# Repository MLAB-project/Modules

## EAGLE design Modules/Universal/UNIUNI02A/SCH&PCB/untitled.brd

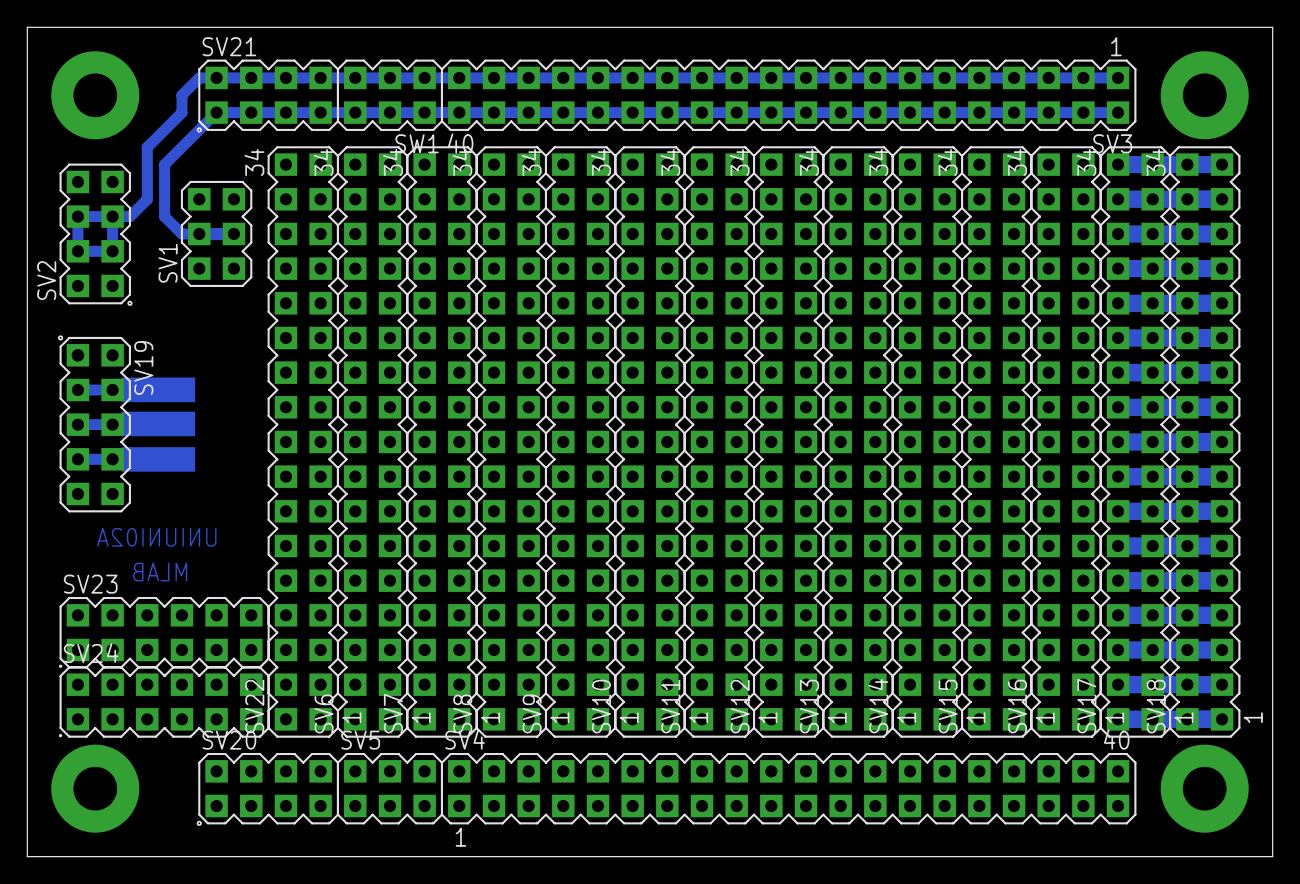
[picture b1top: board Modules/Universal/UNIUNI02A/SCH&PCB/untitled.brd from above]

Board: 2 copper layers, 91.2 x 60.8 mm, 29 parts (0 on the bottom side), 30 nets.

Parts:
SV1, SV5: MA03-2
SV2, SV20, SV21: MA04-2
SV3, SV4: MA20-2
SV6, SV7, SV8, SV9, SV10, SV11, SV12, SV13, SV14, SV15, SV16, SV17, SV18, SV22: MA17-2
SV19: MA05-2
SV23, SV24: MA06-2
SW1: MA03-2
X3, X4, X5, X6: SROUB3M

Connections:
+5V: SV1.3, SV1.4, SV3.2, SV3.4, SV3.6, SV3.8, SV3.10, SV3.12, SV3.14, SV3.16, SV3.18, SV3.20, SV3.22, SV3.24, SV3.26, SV3.28, SV3.30, SV3.32, SV3.34, SV3.36, SV3.38, SV3.40, SV21.1, SV21.3, SV21.5, SV21.7, SW1.2, SW1.4, SW1.6
+12V: SV2.3, SV2.4, SV2.5, SV2.6, SV3.1, SV3.3, SV3.5, SV3.7, SV3.9, SV3.11, SV3.13, SV3.15, SV3.17, SV3.19, SV3.21, SV3.23, SV3.25, SV3.27, SV3.29, SV3.31, SV3.33, SV3.35, SV3.37, SV3.39, SV21.2, SV21.4, SV21.6, SV21.8, SW1.1, SW1.3, SW1.5
GND: SV1.1, SV1.2, SV1.5, SV1.6, SV2.1, SV2.2, SV2.7, SV2.8, SV4.1, SV4.2, SV4.3, SV4.4, SV4.5, SV4.6, SV4.7, SV4.8, SV4.9, SV4.10, SV4.11, SV4.12, SV4.13, SV4.14, SV4.15, SV4.16, SV4.17, SV4.18, SV4.19, SV4.20, SV4.21, SV4.22, SV4.23, SV4.24, SV4.25, SV4.26, SV4.27, SV4.28, SV4.29, SV4.30, SV4.31, SV4.32, SV4.33, SV4.34, SV4.35, SV4.36, SV4.37, SV4.38, SV4.39, SV4.40, SV5.1, SV5.2, SV5.3, SV5.4, SV5.5, SV5.6, SV19.1, SV19.2, SV19.9, SV19.10, SV20.1, SV20.2, SV20.3, SV20.4, SV20.5, SV20.6, SV20.7, SV20.8, X3.P$1, X4.P$1, X5.P$1, X6.P$1
unnamed: SV19.3, SV19.4
unnamed: SV19.5, SV19.6
unnamed: SV19.7, SV19.8
unnamed: SV17.33, SV17.34, SV18.33, SV18.34
unnamed: SV17.31, SV17.32
unnamed: SV17.29, SV17.30, SV18.29, SV18.30
unnamed: SV17.27, SV17.28, SV18.27, SV18.28
unnamed: SV17.25, SV17.26, SV18.25, SV18.26
unnamed: SV17.23, SV17.24
unnamed: SV17.21, SV17.22, SV18.21, SV18.22
unnamed: SV17.19, SV17.20
unnamed: SV17.17, SV17.18
unnamed: SV17.15, SV17.16
unnamed: SV17.13, SV17.14, SV18.13, SV18.14
unnamed: SV17.11, SV17.12, SV18.11, SV18.12
unnamed: SV17.9, SV17.10
unnamed: SV17.7, SV17.8, SV18.7, SV18.8
unnamed: SV17.5, SV17.6, SV18.5, SV18.6
unnamed: SV17.3, SV17.4, SV18.3, SV18.4
unnamed: SV17.1, SV17.2
unnamed: SV18.31, SV18.32
unnamed: SV18.23, SV18.24
unnamed: SV18.19, SV18.20
unnamed: SV18.17, SV18.18
unnamed: SV18.15, SV18.16
unnamed: SV18.9, SV18.10
unnamed: SV18.1, SV18.2

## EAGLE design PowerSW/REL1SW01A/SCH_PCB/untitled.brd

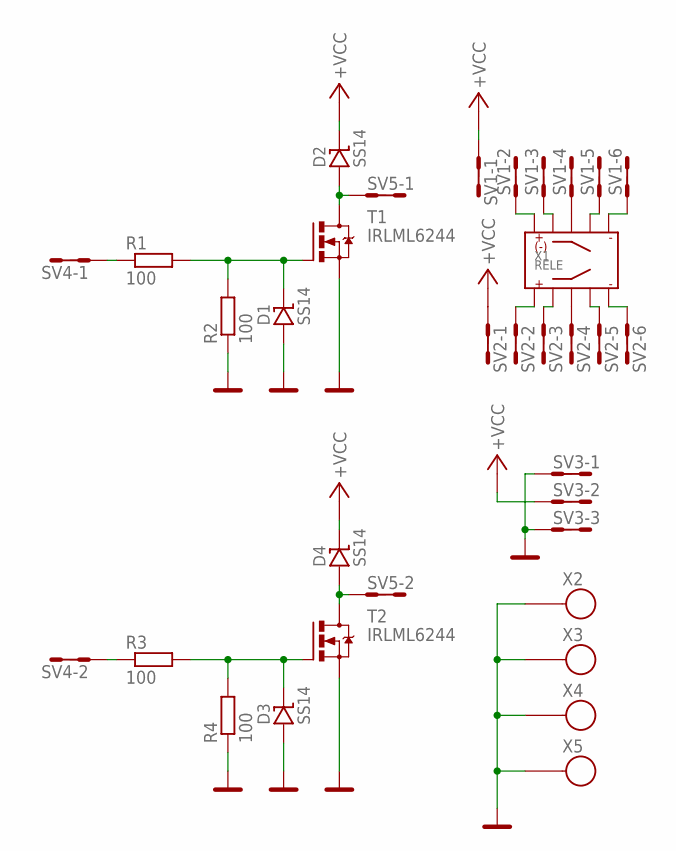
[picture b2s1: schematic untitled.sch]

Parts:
D1, D2, D3, D4: SS14; SMA
R1, R2, R3, R4: 100; 0805
SV1, SV2: MA06-2
SV3: MA03-2
SV4, SV5: MA02-2
T1, T2: IRLML6244; SOT23
X1: RELE
X2, X3, X4, X5: SROUB3M

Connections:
+VCC: D2.K, D4.K, SV1.1, SV1.2, SV2.1, SV2.2, SV3.3, SV3.4
GND: D1.A, D3.A, R2.1, R4.1, SV3.1, SV3.2, SV3.5, SV3.6, T1.2 (S), T2.2 (S), X2.P$1, X3.P$1, X4.P$1, X5.P$1
unnamed: D2.A, SV5.1, SV5.2, T1.3 (D)
unnamed: D1.K, R1.2, R2.2, T1.1 (G)
unnamed: D4.A, SV5.3, SV5.4, T2.3 (D)
unnamed: D3.K, R3.2, R4.2, T2.1 (G)
unnamed: SV1.3, SV1.4, X1.10
unnamed: SV1.5, SV1.6, X1.9
unnamed: SV1.7, SV1.8, X1.8
unnamed: SV1.9, SV1.10, X1.7
unnamed: SV1.11, SV1.12, X1.6
unnamed: SV2.3, SV2.4, X1.1
unnamed: SV2.5, SV2.6, X1.2
unnamed: SV2.7, SV2.8, X1.3
unnamed: SV2.9, SV2.10, X1.4
unnamed: SV2.11, SV2.12, X1.5
unnamed: R1.1, SV4.1, SV4.2
unnamed: R3.1, SV4.3, SV4.4

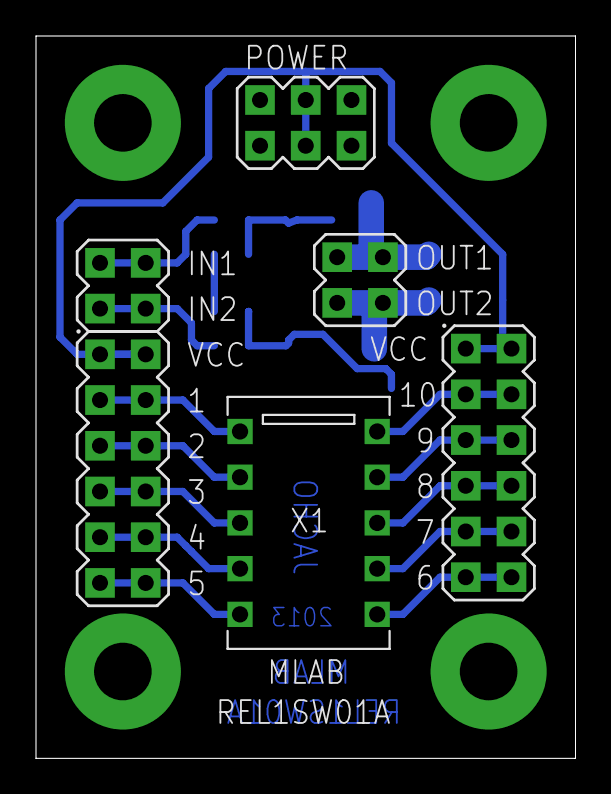
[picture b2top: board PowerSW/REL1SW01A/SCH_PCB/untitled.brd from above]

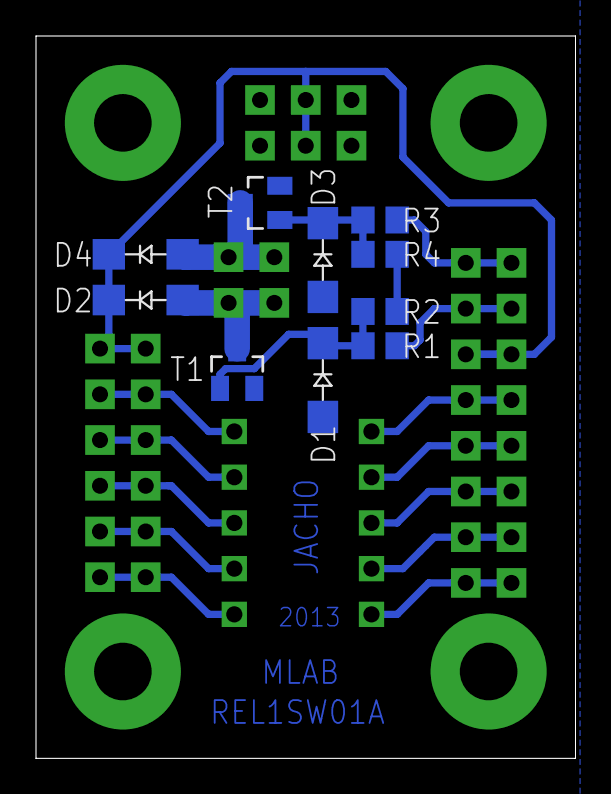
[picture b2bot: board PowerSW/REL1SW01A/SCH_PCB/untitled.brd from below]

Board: 2 copper layers, 30.0 x 40.1 mm, 20 parts (10 on the bottom side), 18 nets.

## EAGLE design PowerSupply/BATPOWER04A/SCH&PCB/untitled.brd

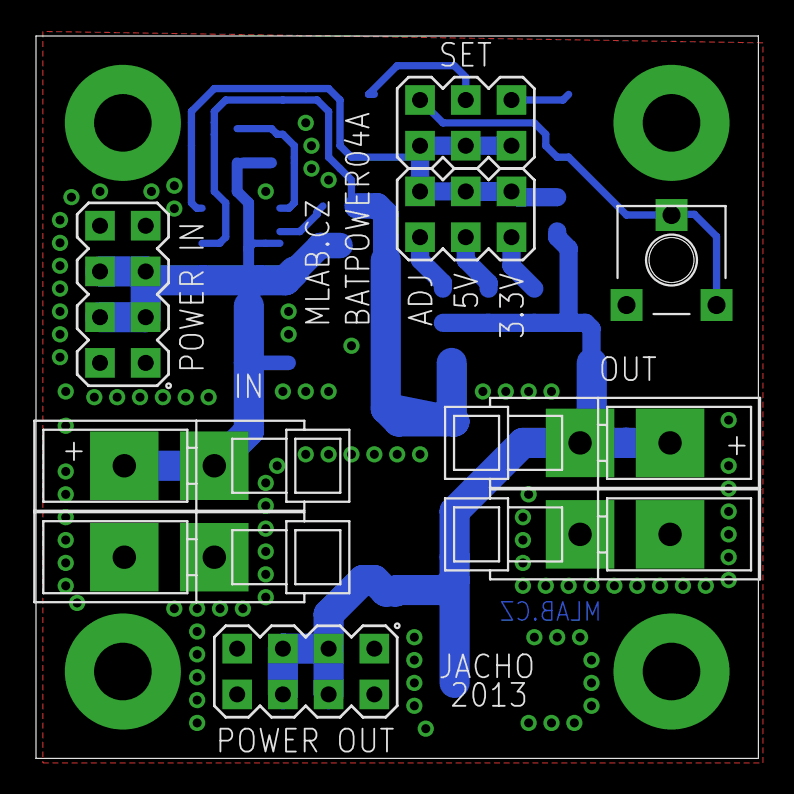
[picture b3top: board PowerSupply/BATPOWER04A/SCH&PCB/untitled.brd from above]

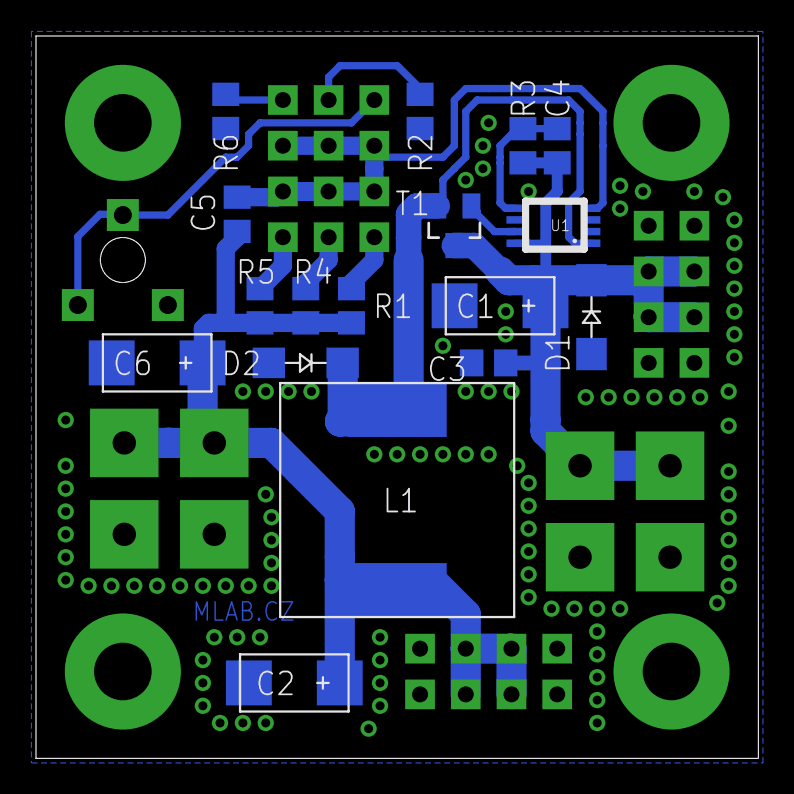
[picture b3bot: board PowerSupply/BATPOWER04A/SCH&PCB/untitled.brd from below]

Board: 2 copper layers, 40.1 x 40.1 mm, 30 parts (17 on the bottom side), 13 nets.

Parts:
C1: 47u; C
C2, C6: 100u; C
C3: 100n; C0805
C4: 1n; C0805
C5: 100p; C0805
D1: M4; SMA
D2: 15MQ040N; SMA
L1: 22u; DE1205-10
P1: TRIM_CA6XV
R1: 0805
R2, R6: 20k; 0805
R3: 22k; 0805
R4: 60k4; 0805
R5: 33k; 0805
SV1, SV2: MA04-2
SV3, SV4, SV5, SV6: WAGO256
SW1, SW2: MA03-2
T1: AP2305AGN; SOT23
U1: LM3485; MSOP-8
X1, X2, X3, X4: SROUB3M

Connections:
GND: C1.-, C2.-, C3.1, C6.-, D1.A, D2.A, P1.1, R2.1, R6.1, SV1.1, SV1.2, SV1.7, SV1.8, SV2.1, SV2.2, SV2.7, SV2.8, SV3.1, SV3.A1, SV5.1, SV5.A1, U1.2, U1.6
unnamed: T1.1, U1.7
unnamed: C1.+, C3.2, C4.2, D1.K, R3.2, SV1.3, SV1.4, SV1.5, SV1.6, SV4.1, SV4.A1, T1.3, U1.8
unnamed: C5.1, SW1.2, SW1.4, SW1.6, SW2.1, SW2.3, SW2.5, U1.4
unnamed: C4.1, R3.1, U1.5
unnamed: R1.1, SW1.1
unnamed: D2.K, L1.P$1, T1.2, U1.1
unnamed: R4.1, SW1.3
unnamed: C2.+, C5.2, C6.+, L1.P$2, R1.2, R4.2, R5.2, SV2.3, SV2.4, SV2.5, SV2.6, SV6.1, SV6.A1
unnamed: R5.1, SW1.5
unnamed: R2.2, SW2.4
unnamed: R6.2, SW2.6
unnamed: P1.2, P1.3, SW2.2

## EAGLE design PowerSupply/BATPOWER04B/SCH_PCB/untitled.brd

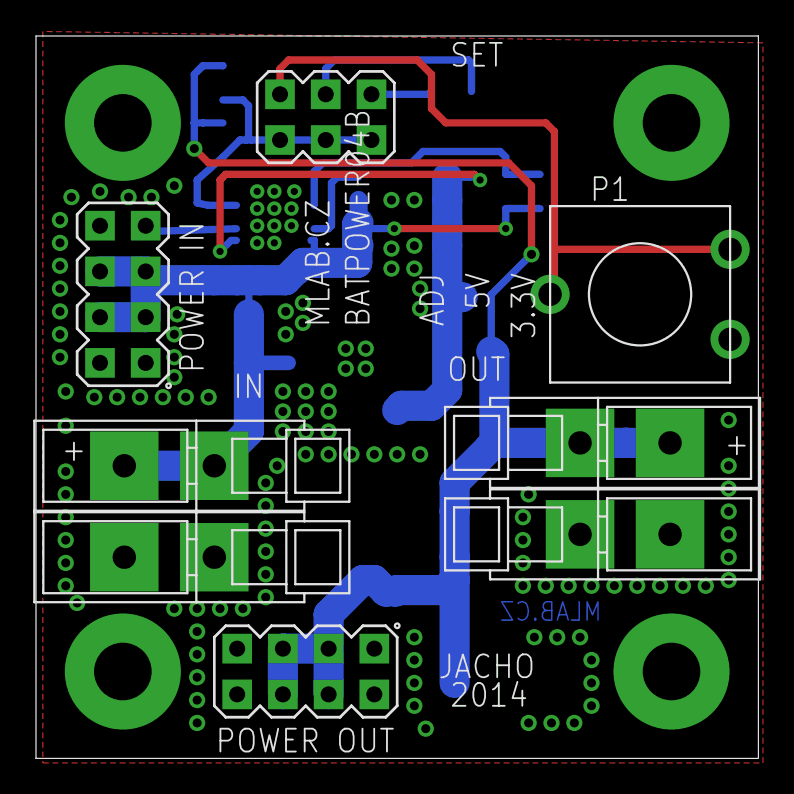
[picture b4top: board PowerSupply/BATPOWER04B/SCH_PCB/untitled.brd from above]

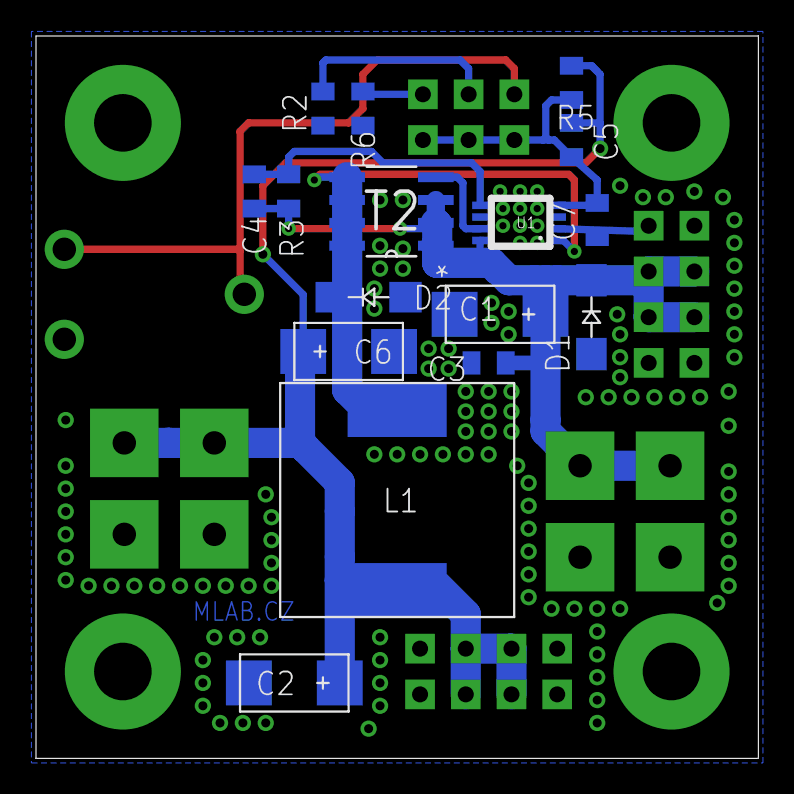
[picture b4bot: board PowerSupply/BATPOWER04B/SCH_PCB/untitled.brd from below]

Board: 2 copper layers, 40.1 x 40.1 mm, 28 parts (16 on the bottom side), 10 nets.

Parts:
C1: 47u; C
C2, C6: 100u; C
C3: 100n; C0805
C4: 1n; C0805
C5: 100p; C0805
C7: 470p; C0805
D1: M4; SMA
D2: 15MQ040N; SMA
L1: 22u; DE1205-10
P1: TRIM_CA9MTV10
R2, R6: 20k; 0805
R3: 22k; 0805
R5: 33k; 0805
SV1, SV2: MA04-2
SV3, SV4, SV5, SV6: WAGO256
SW2: MA03-2
T2: IRF7416; SO8
U1: LM3485; MSOP-8
X1, X2, X3, X4: SROUB3M

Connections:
GND: C1.-, C2.-, C3.1, C6.-, C7.1, D1.A, D2.A, P1.1, R2.1, R6.1, SV1.1, SV1.2, SV1.7, SV1.8, SV2.1, SV2.2, SV2.7, SV2.8, SV3.1, SV3.A1, SV5.1, SV5.A1, U1.2, U1.6
unnamed: T2.4, U1.7
unnamed: C1.+, C3.2, C4.2, D1.K, R3.2, SV1.3, SV1.4, SV1.5, SV1.6, SV4.1, SV4.A1, T2.1, T2.2, T2.3, U1.8
unnamed: C5.1, C7.2, R5.1, SW2.1, SW2.3, SW2.5, U1.4
unnamed: C4.1, R3.1, U1.5
unnamed: C2.+, C5.2, C6.+, L1.P$2, R5.2, SV2.3, SV2.4, SV2.5, SV2.6, SV6.1, SV6.A1
unnamed: D2.K, L1.P$1, T2.5, T2.6, T2.7, T2.8, U1.1
unnamed: R2.2, SW2.4
unnamed: R6.2, SW2.6
unnamed: P1.2, P1.3, SW2.2

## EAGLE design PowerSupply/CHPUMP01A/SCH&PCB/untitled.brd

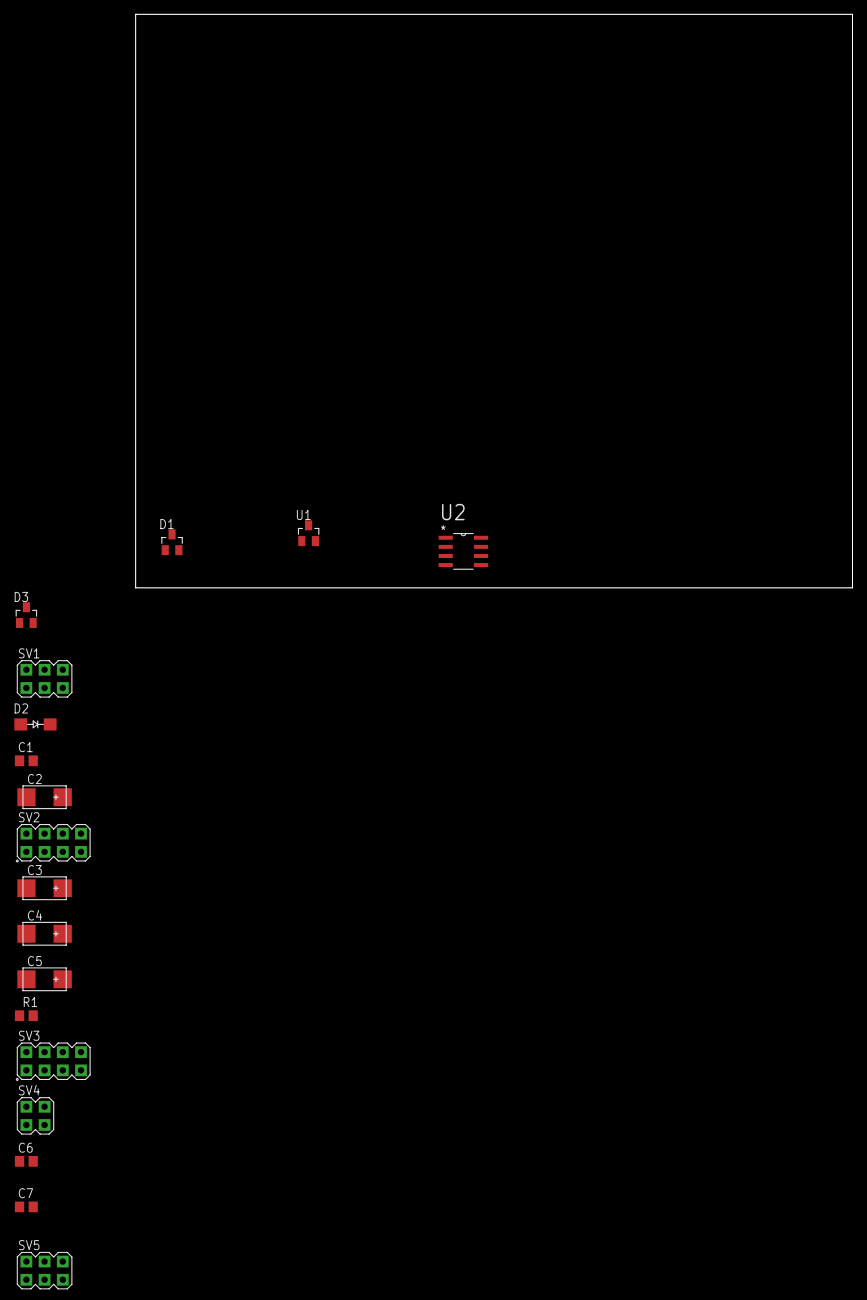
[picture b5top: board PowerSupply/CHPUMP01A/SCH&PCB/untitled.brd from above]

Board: 2 copper layers, 100.0 x 80.0 mm, 18 parts (0 on the bottom side), 10 nets, no tracks yet.

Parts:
C1, C6: 100nF; C0805
C2: 47uF; C
C3, C4, C5: C
C7: 1uF; C0805
D1, D3: TS2431A; SOT23
D2: M4; SMA
R1: 0805
SV1, SV5: MA03-2
SV2, SV3: MA04-2
SV4: MA02-2
U1: MCP1541T; SOT23
U2: TC682E; SO8

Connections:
+5V: C1.1, C2.+, C6.1, D2.K, SV1.3, SV1.4, U1.1, U2.6
-VCC: C5.+, R1.1, SV2.3, SV2.4, SV2.5, SV2.6, U2.4
GND: C1.2, C2.-, C5.-, C6.2, C7.2, D1.1, D1.2, D2.A, SV1.1, SV1.2, SV1.5, SV1.6, SV2.1, SV2.2, SV2.7, SV2.8, SV3.1, SV3.2, SV3.7, SV3.8, SV5.1, SV5.2, SV5.5, SV5.6, U1.3, U2.5
unnamed: C3.-, U2.1
unnamed: C3.+, U2.7
unnamed: C4.+, U2.2
unnamed: C4.-, U2.3
unnamed: D3.3, R1.2, SV3.5, SV3.6, SV4.3, SV4.4
unnamed: D1.3, D3.1, D3.2, SV3.3, SV3.4, SV4.1, SV4.2
unnamed: C7.1, SV5.3, SV5.4, U1.2

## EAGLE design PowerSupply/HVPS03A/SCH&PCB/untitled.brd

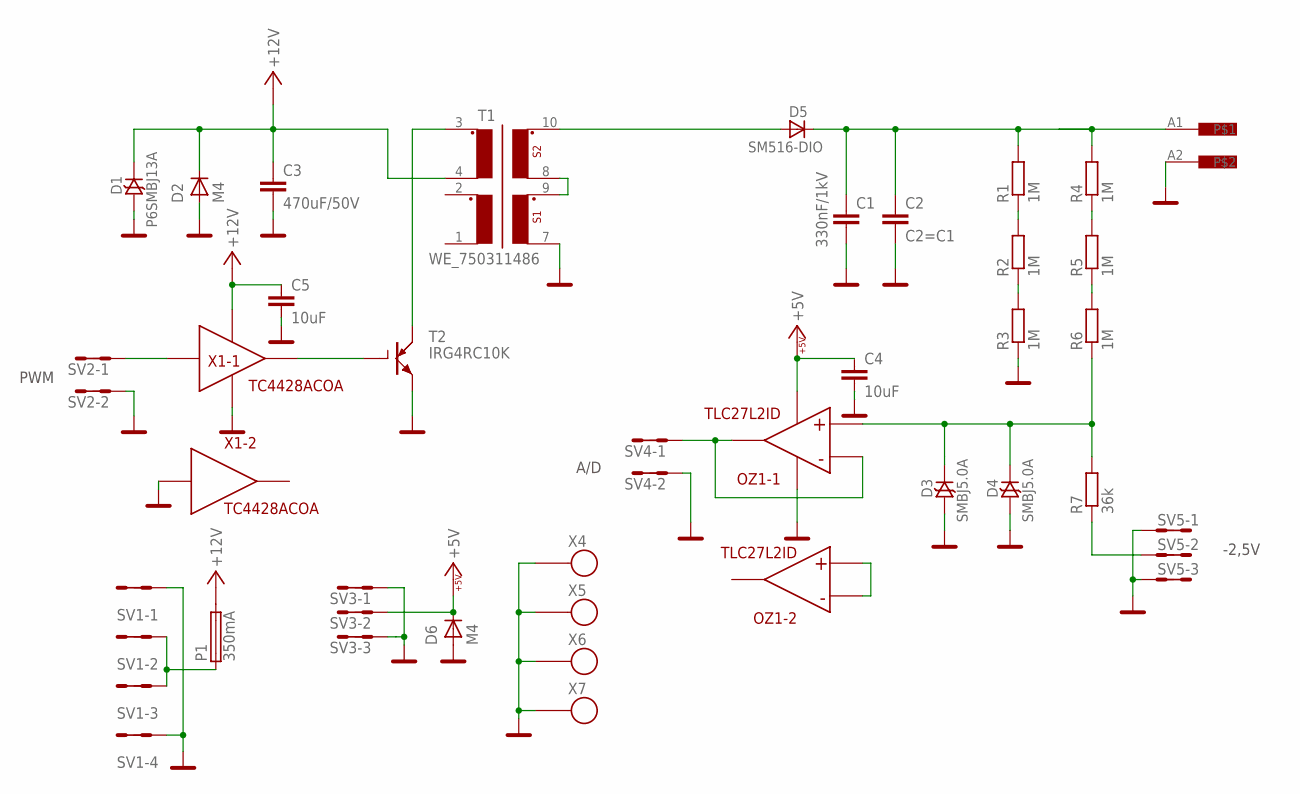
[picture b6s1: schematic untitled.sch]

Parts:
C1: 330nF/1kV; C22,5MM
C2: C2=C1; C27,5MM
C3: 470uF/50V; C050-025X075
C4, C5: 10uF; C0805
D1: P6SMBJ13A; SMB
D2, D6: M4; SMA
D3, D4: SMBJ5.0A; SMA
D5: SM516-DIO; MELF
OZ1: TLC27L2ID; SOP8
P1: 350mA; 1812
R1, R2, R3, R4, R5, R6: 1M; 1206
R7: 36k; 0805
SV1: MA04-2
SV2, SV4: MA02-2
SV3, SV5: MA03-2
T1: WE_750311486; TRAFO75311486
T2: IRG4RC10K; DPAK
X1: TC4428ACOA; SO8
X2: SVORKOVNICE2X_PC; SVORKOVNICE_10,16MM
X4, X5, X6, X7: SROUB3M

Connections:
+5V: C4.1, D6.K (C), OZ1.4 (GND), SV3.3, SV3.4
+12V: C3.1, C5.1, D1.K, D2.K (C), P1.2, T1.4, X1.6 (VDD)
GND: C1.P$3 (2), C2.P$2 (2), C3.2, C4.2, C5.2, D1.A, D2.A, D3.A, D4.A, D6.A, OZ1.8 (VDD), R3.1, SV1.1, SV1.2, SV1.7, SV1.8, SV2.3, SV2.4, SV3.1, SV3.2, SV3.5, SV3.6, SV4.3, SV4.4, SV5.1, SV5.2, SV5.5, SV5.6, T1.7, T2.S (E), X1.3 (GND), X1.4 (-), X2.A2, X4.P$1, X5.P$1, X6.P$1, X7.P$1
unnamed: T1.3, T2.D (C)
unnamed: T2.G, X1.7 (VOUT)
unnamed: SV2.1, SV2.2, X1.2 (-)
unnamed: T1.8, T1.9
unnamed: D5.A, T1.10
unnamed: C1.P$2 (1), C2.P$1 (1), D5.C (K), R1.2, R4.2, X2.A1
unnamed: R1.1, R2.2
unnamed: R2.1, R3.2
unnamed: R4.1, R5.2
unnamed: R5.1, R6.2
unnamed: D3.K, D4.K, OZ1.3 (+), R6.1, R7.2
unnamed: OZ1.1 (VOUT), OZ1.2 (-), SV4.1, SV4.2
unnamed: P1.1, SV1.3, SV1.4, SV1.5, SV1.6
unnamed: OZ1.5 (+), OZ1.6 (-)
unnamed: R7.1, SV5.3, SV5.4

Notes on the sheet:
PWM
A/D
-2,5V

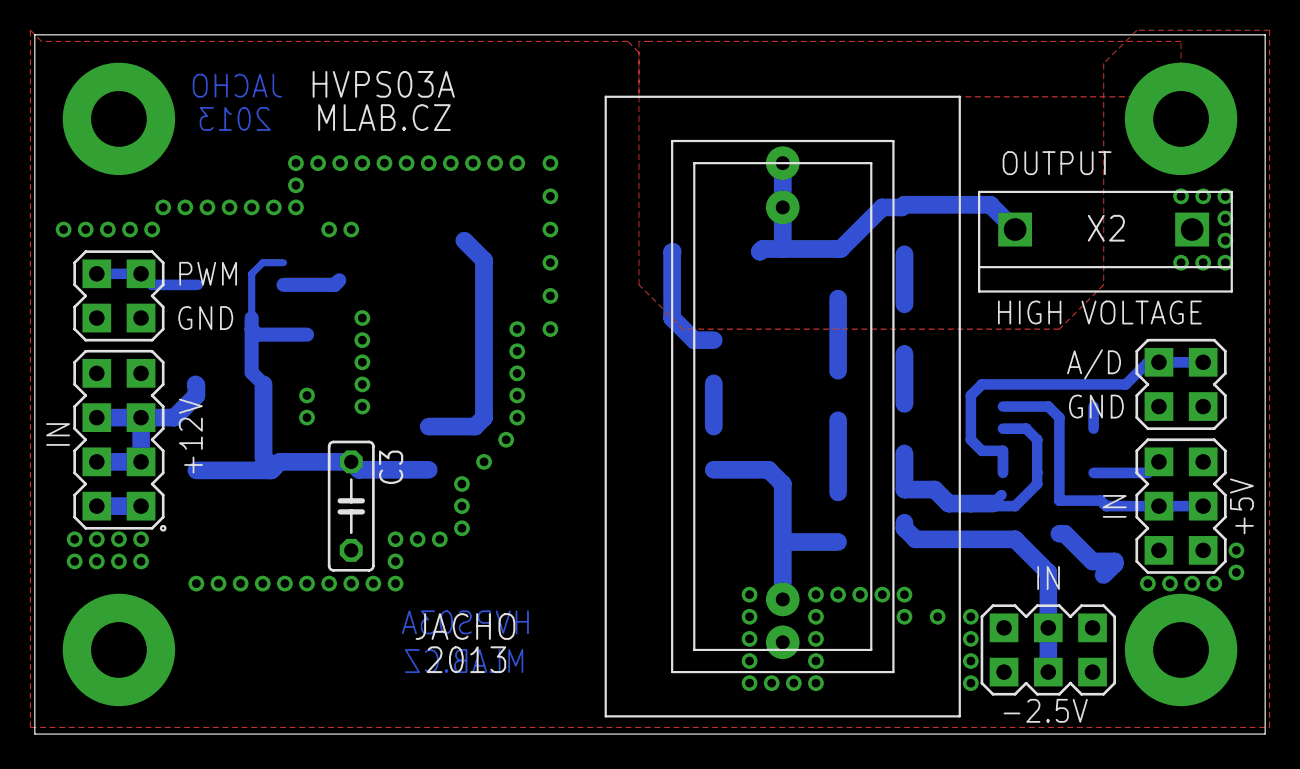
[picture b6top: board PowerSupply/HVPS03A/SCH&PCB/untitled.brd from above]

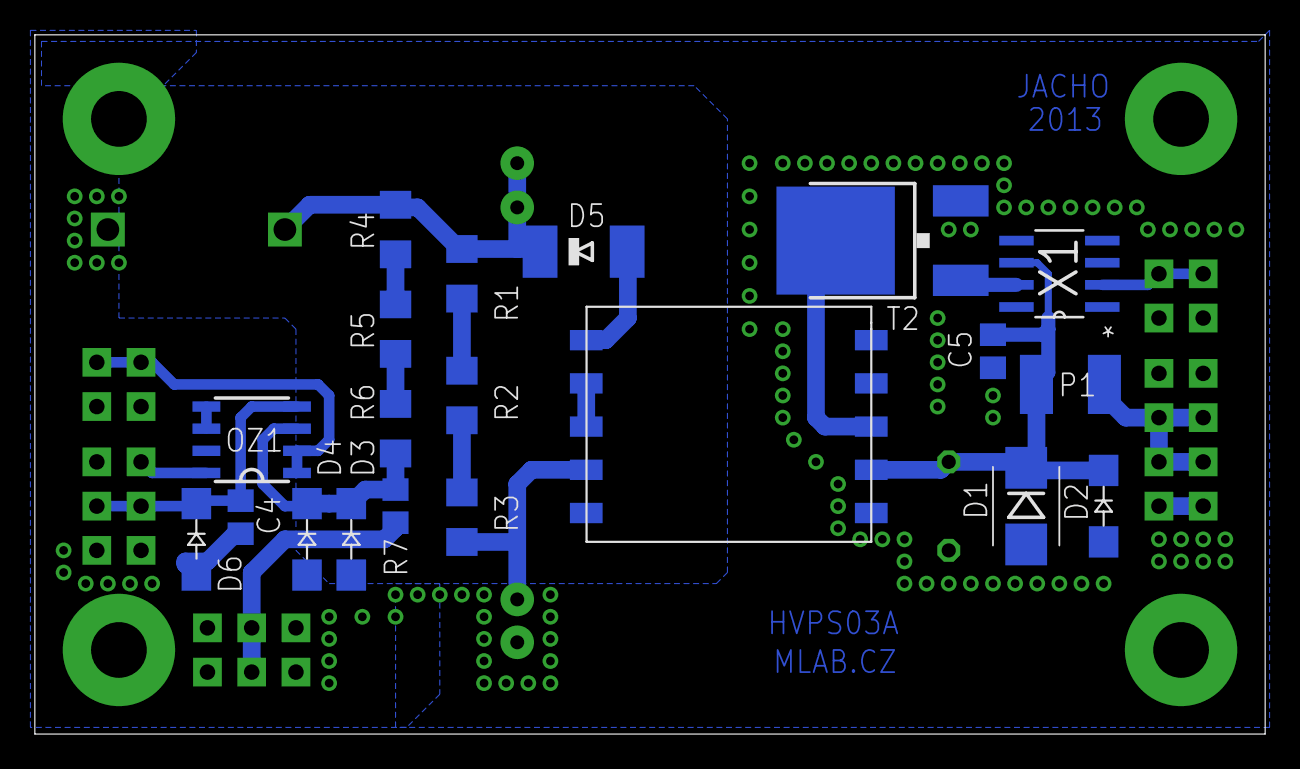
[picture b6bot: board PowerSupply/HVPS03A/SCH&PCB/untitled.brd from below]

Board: 2 copper layers, 70.6 x 40.1 mm, 33 parts (20 on the bottom side), 18 nets.
